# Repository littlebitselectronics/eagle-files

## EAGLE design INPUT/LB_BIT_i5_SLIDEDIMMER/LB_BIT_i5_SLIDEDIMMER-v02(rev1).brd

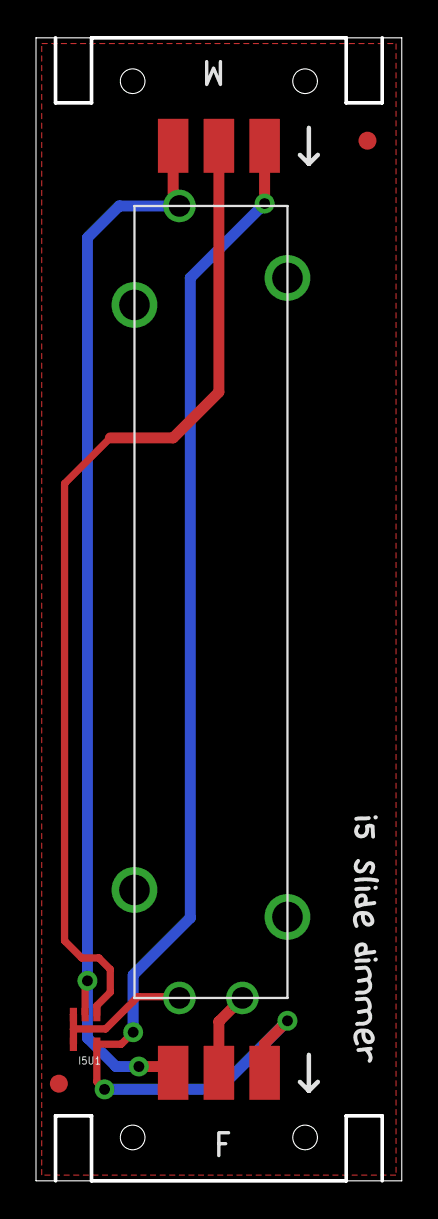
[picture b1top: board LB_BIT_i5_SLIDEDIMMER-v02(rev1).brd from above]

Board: 2 copper layers, 20.3 x 63.5 mm, 23 parts (0 on the bottom side), 5 nets.

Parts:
I5BSF: BITSNAP_FEMALE
I5BSM: BITSNAP_MALE
I5FD1, I5FD2: FIDUCIAL1X2; FIDUCIAL-1X2
I5R1: POT-SLIDE-30MM
I5U1: LV321; SC70
U$1, U$9, U$13: I
U$2: 5
U$3: S
U$4: L
U$5: OSHW-LOGOL; OSHW-LOGO-L
U$7: OSHW_FILLX150_NOTEXT
U$8: LB_V02
U$10, U$12: D
U$11, U$16: E
U$14, U$15: M
U$17: R
U$18: LB_CREDITS_V2

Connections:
GND: I5BSF.GND, I5BSM.GND, I5R1.3, I5U1.2
unnamed: I5R1.1, I5U1.3, I5U1.4
unnamed: I5BSM.SIG, I5U1.1
POT: I5BSF.SIG, I5R1.2
VCC: I5BSF.VCC, I5BSM.VCC, I5U1.5

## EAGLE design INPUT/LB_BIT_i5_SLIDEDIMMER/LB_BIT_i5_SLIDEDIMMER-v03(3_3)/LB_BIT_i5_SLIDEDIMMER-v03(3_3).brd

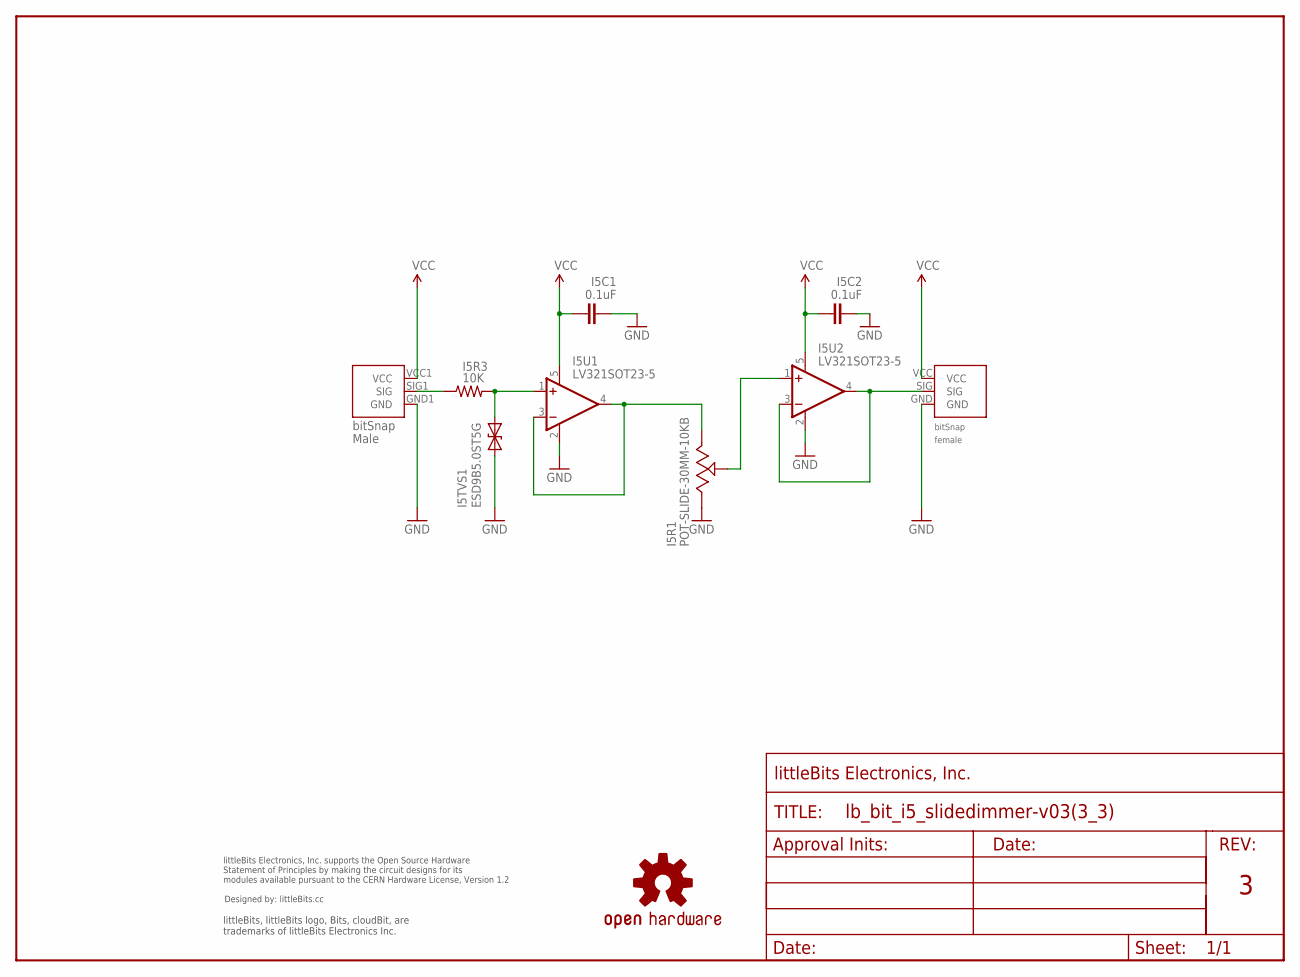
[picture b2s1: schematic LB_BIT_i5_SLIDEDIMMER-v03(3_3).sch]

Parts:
FRAME2: FRAME-LETTER-OHWOHW; FABDWG01-OHW
I5BSF1: BITSNAP_V03_FEMALE
I5BSM1: BITSNAP_V03_MALE
I5C1, I5C2: 0.1uF; CAP-0603
I5R1: POT-SLIDE-30MM-10KB; POT-SLIDE-30MM
I5R3: 10K; RES-0603
I5TVS1: ESD9B5.0ST5G; SOD-923
I5U1, I5U2: LV321SOT23-5; SOT23-5
U$1: OSHWCREDIT
U$5: OSHW-LOGOL; OSHW-LOGO-L

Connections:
GND: I5BSF1.GND, I5BSM1.GND1 (GND), I5C1.2, I5C2.2, I5R1.3, I5TVS1.1 (A), I5U1.2 (V-), I5U2.2 (V-)
unnamed: I5R1.1, I5U1.3 (-IN), I5U1.4 (OUT)
unnamed: I5BSM1.SIG1 (SIG), I5R3.1
unnamed: I5R3.2, I5TVS1.2 (C), I5U1.1 (+IN)
unnamed: I5R1.2, I5U2.1 (+IN)
unnamed: I5BSF1.SIG, I5U2.3 (-IN), I5U2.4 (OUT)
VCC: I5BSF1.VCC, I5BSM1.VCC1 (VCC), I5C1.1, I5C2.1, I5U1.5 (V+), I5U2.5 (V+)

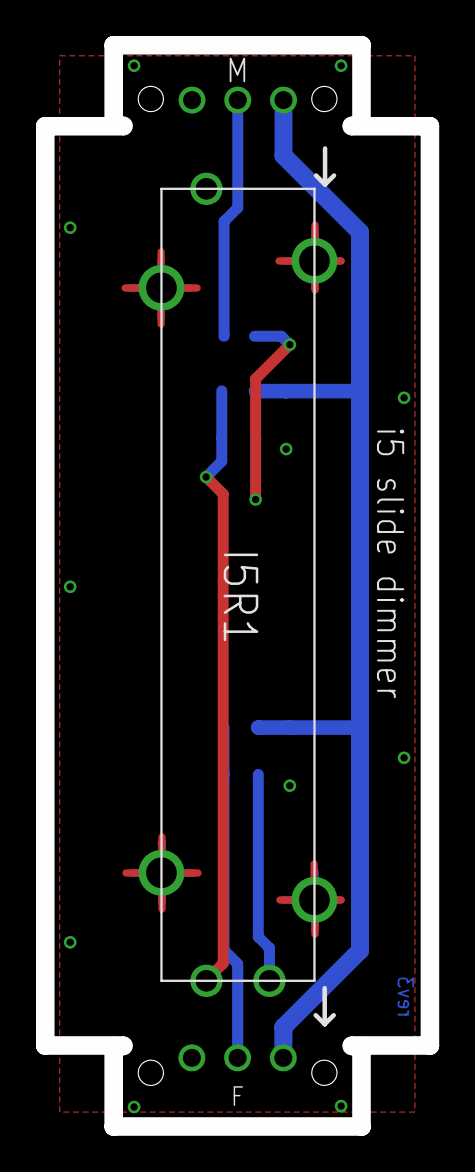
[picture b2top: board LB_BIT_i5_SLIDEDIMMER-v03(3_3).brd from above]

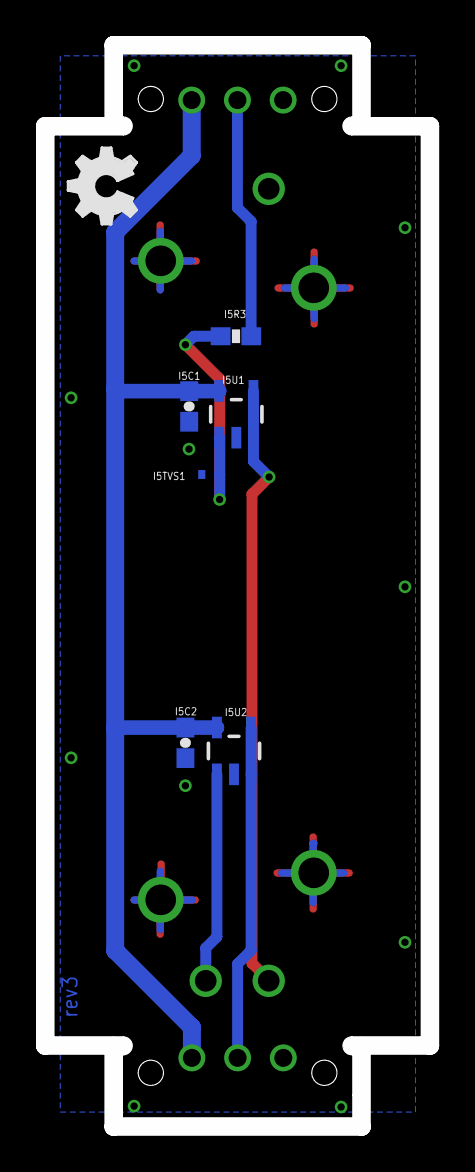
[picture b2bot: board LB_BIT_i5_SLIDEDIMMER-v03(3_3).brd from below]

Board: 2 copper layers, 21.4 x 60.1 mm, 13 parts (6 on the bottom side), 7 nets.

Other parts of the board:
U$7: OSHW_FILLX150_NOTEXT

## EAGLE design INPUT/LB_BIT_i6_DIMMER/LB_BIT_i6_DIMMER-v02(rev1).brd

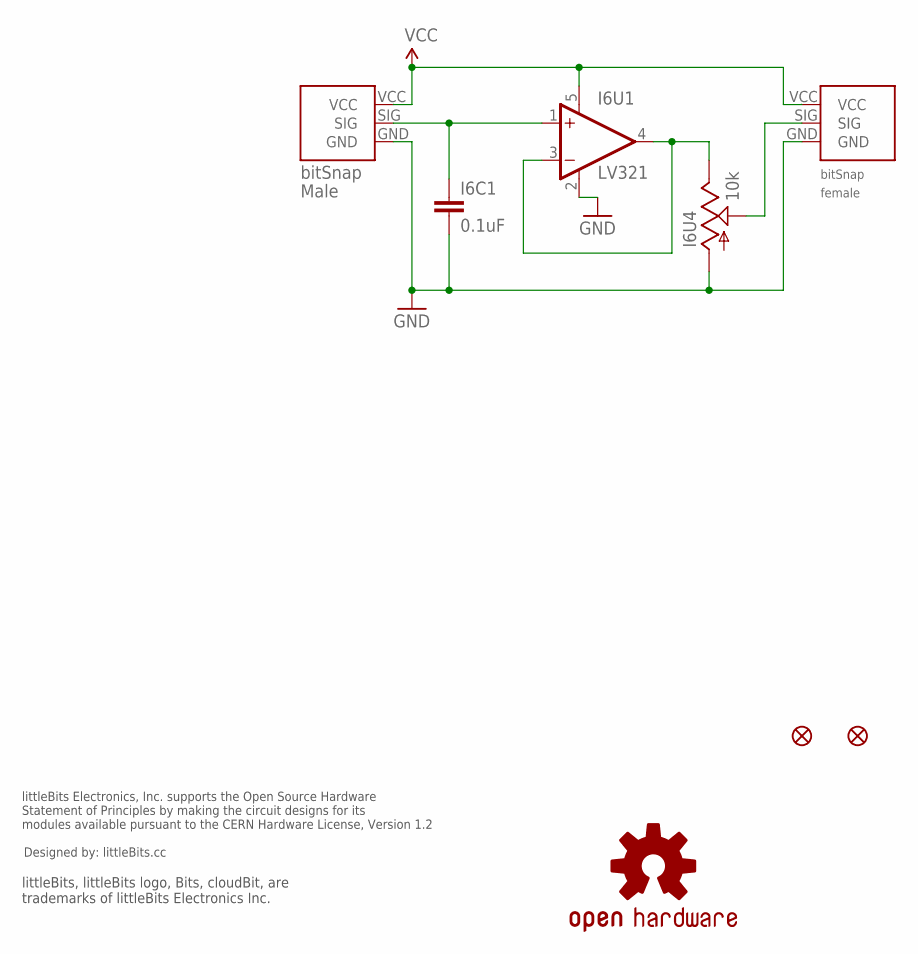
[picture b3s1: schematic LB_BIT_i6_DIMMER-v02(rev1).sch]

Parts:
I6BSF: BITSNAP_FEMALE
I6BSM: BITSNAP_MALE
I6C1: 0.1uF; 0603-CAP
I6U1: LV321; SC70-5
I6U4: 10k; ALPS_POT
JP1, JP2: FIDUCIAL1X2.5; FIDUCIAL-1X2.5
U$1: OSHWCREDIT
U$3: OSHW-LOGOL; OSHW-LOGO-L

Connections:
GND: I6BSF.GND, I6BSM.GND, I6C1.2, I6U1.2 (V-), I6U4.P$3 (A)
unnamed: I6U1.3 (-IN), I6U1.4 (OUT), I6U4.P$1 (E)
POT: I6BSF.SIG, I6U4.P$2 (S)
SIG: I6BSM.SIG, I6C1.1, I6U1.1 (+IN)
VCC: I6BSF.VCC, I6BSM.VCC, I6U1.5 (V+)

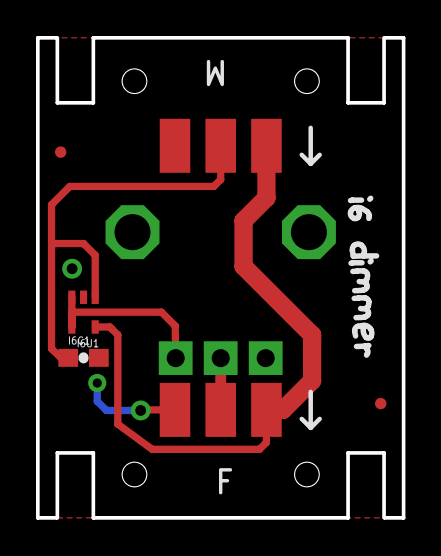
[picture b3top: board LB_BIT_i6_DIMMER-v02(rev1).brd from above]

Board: 2 copper layers, 20.3 x 26.7 mm, 9 parts (0 on the bottom side), 5 nets.

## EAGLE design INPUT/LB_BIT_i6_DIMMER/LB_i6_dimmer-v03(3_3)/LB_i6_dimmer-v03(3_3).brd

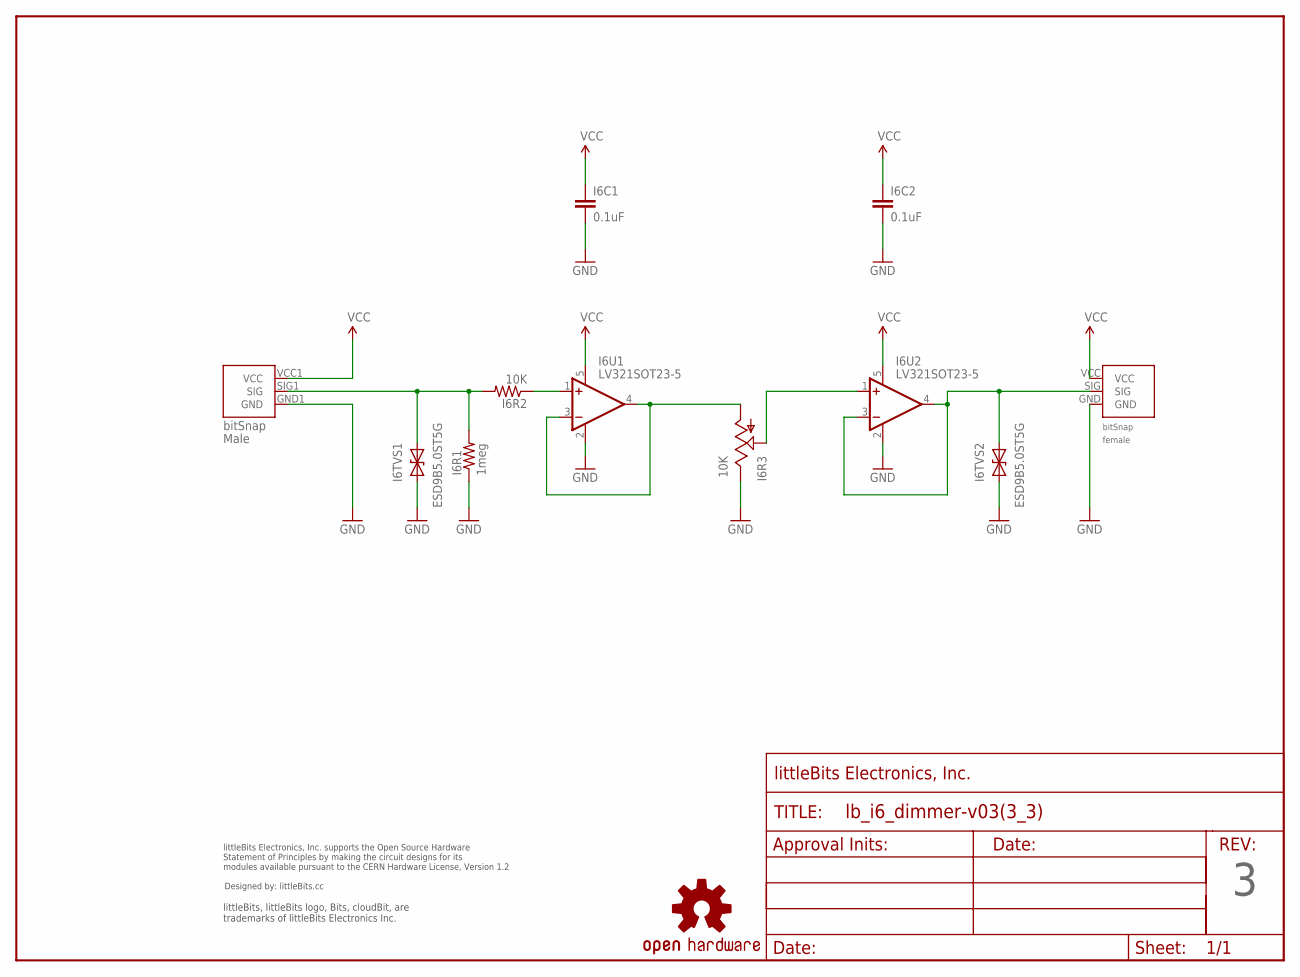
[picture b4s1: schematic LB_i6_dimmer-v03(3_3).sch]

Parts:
FRAME1: FRAME-LETTER-OHWOHW; FABDWG01-OHW
I6BSF1: BITSNAP_V03_FEMALE
I6BSM1: BITSNAP_V03_MALE
I6C1, I6C2: 0.1uF; CAP-0603
I6R1: 1meg; RES-0603
I6R2: 10K; RES-0603
I6R3: 10K; ALPS_POT
I6TVS1, I6TVS2: ESD9B5.0ST5G; SOD-923
I6U1, I6U2: LV321SOT23-5; SOT23-5
U$3: OSHW-LOGOL; OSHW-LOGO-L
U$4: LB_CREDITS; OSHWCREDIT

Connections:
GND: I6BSF1.GND, I6BSM1.GND1 (GND), I6C1.2, I6C2.2, I6R1.1, I6R3.P$1 (E), I6TVS1.1 (A), I6TVS2.1 (A), I6U1.2 (V-), I6U2.2 (V-)
unnamed: I6R3.P$3 (A), I6U1.3 (-IN), I6U1.4 (OUT)
unnamed: I6R2.1, I6U1.1 (+IN)
unnamed: I6BSF1.SIG, I6TVS2.2 (C), I6U2.3 (-IN), I6U2.4 (OUT)
unnamed: I6R3.P$2 (S), I6U2.1 (+IN)
SIG: I6BSM1.SIG1 (SIG), I6R1.2, I6R2.2, I6TVS1.2 (C)
VCC: I6BSF1.VCC, I6BSM1.VCC1 (VCC), I6C1.1, I6C2.1, I6U1.5 (V+), I6U2.5 (V+)

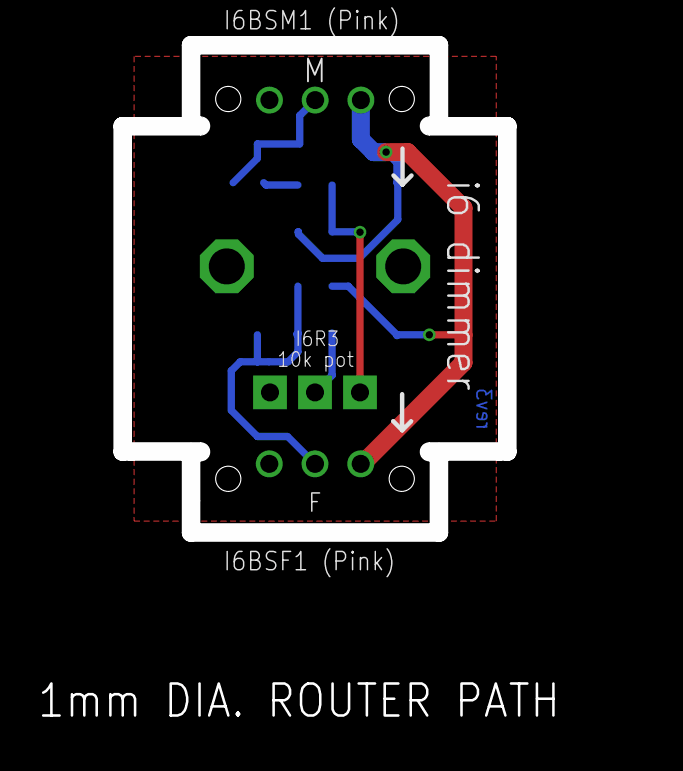
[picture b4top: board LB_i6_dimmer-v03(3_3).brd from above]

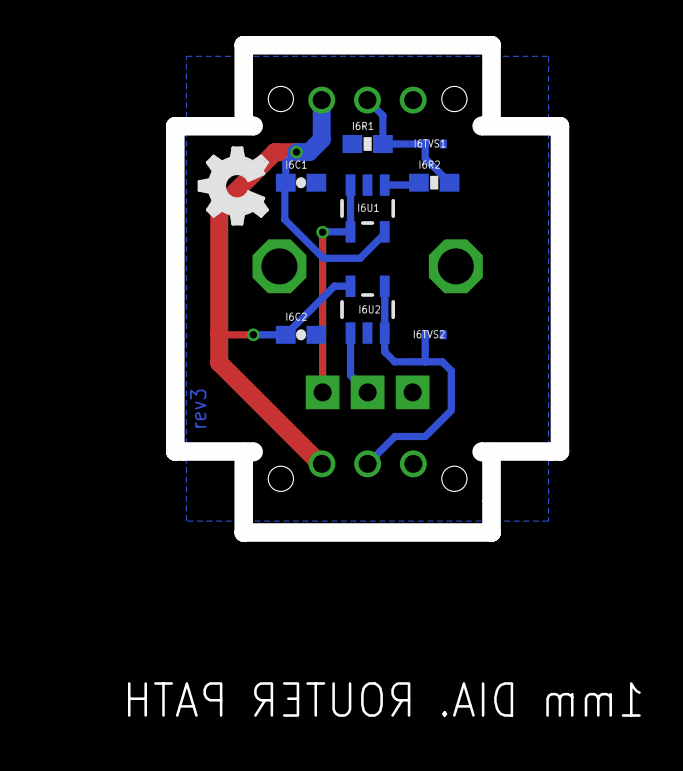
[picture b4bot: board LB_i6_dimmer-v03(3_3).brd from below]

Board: 2 copper layers, 21.4 x 27.1 mm, 15 parts (8 on the bottom side), 7 nets.

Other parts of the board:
U$1: OSHW_FILLX150_NOTEXT

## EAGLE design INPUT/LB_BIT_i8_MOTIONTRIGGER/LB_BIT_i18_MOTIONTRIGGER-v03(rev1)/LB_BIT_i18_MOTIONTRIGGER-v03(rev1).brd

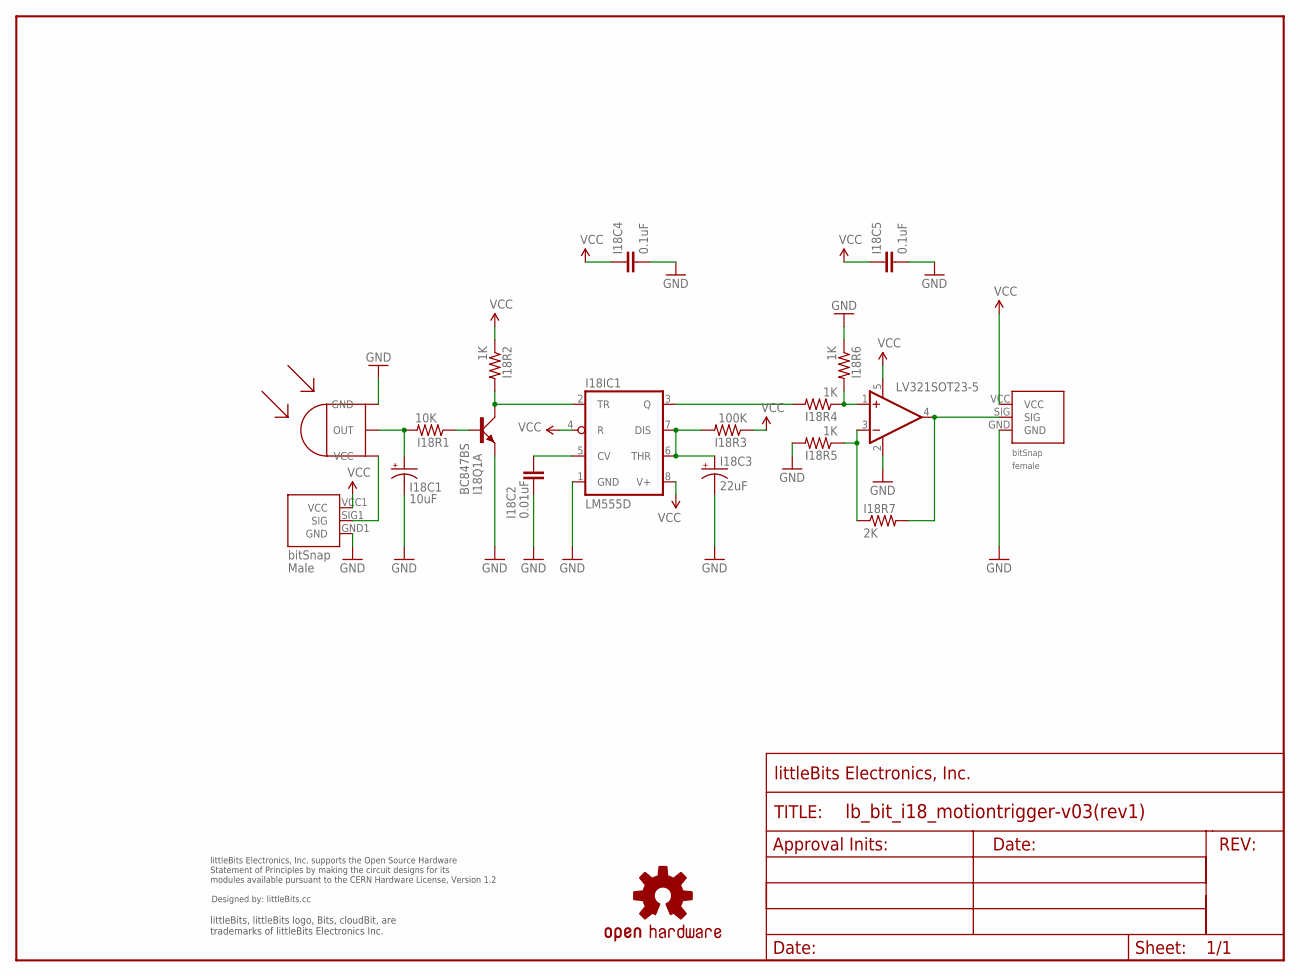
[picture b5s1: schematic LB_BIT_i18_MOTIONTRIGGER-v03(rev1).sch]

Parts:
I18BSF: BITSNAP_V03_FEMALE
I18BSM: BITSNAP_V03_MALE
I18C1: 10uF; EIA3216
I18C2: 0.01uF; 0603-CAP
I18C3: 22uF; EIA3216
I18C4, I18C5: 0.1uF; 0603-CAP
I18IC1: LM555D; SO08
I18Q1: BC847BS; SOT363_PHILIPS
I18R1: 10K; 0603-RES
I18R2, I18R4, I18R5, I18R6: 1K; 0603-RES
I18R3: 100K; 0603-RES
I18R7: 2K; 0603-RES
I18U1: PIR-EKMC1601112
I18U2: LV321SOT23-5; SOT23-5
U$1: OSHWCREDIT
U$2: FRAME-LETTER-OHWOHW; FABDWG01-OHW
U$8: OSHW-LOGOL; OSHW-LOGO-L

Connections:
GND: I18BSF.GND, I18BSM.GND1 (GND), I18C1.C (-), I18C2.2, I18C3.C (-), I18C4.2, I18C5.2, I18IC1.1 (GND), I18Q1.1 (E), I18R5.2, I18R6.1, I18U1.GND, I18U2.2 (V-)
unnamed: I18BSM.SIG1 (SIG), I18U1.VCC
unnamed: I18IC1.2 (TR), I18Q1.6 (C), I18R2.2
unnamed: I18C1.A (+), I18R1.2, I18U1.OUT
unnamed: I18Q1.2 (B), I18R1.1
unnamed: I18C2.1, I18IC1.5 (CV)
unnamed: I18C3.A (+), I18IC1.6 (THR), I18IC1.7 (DIS), I18R3.2
unnamed: I18IC1.3 (Q), I18R4.2
unnamed: I18R4.1, I18R6.2, I18U2.1 (+IN)
unnamed: I18R5.1, I18R7.1, I18U2.3 (-IN)
unnamed: I18BSF.SIG, I18R7.2, I18U2.4 (OUT)
VCC: I18BSF.VCC, I18BSM.VCC1 (VCC), I18C4.1, I18C5.1, I18IC1.4 (R), I18IC1.8 (V+), I18R2.1, I18R3.1, I18U2.5 (V+)

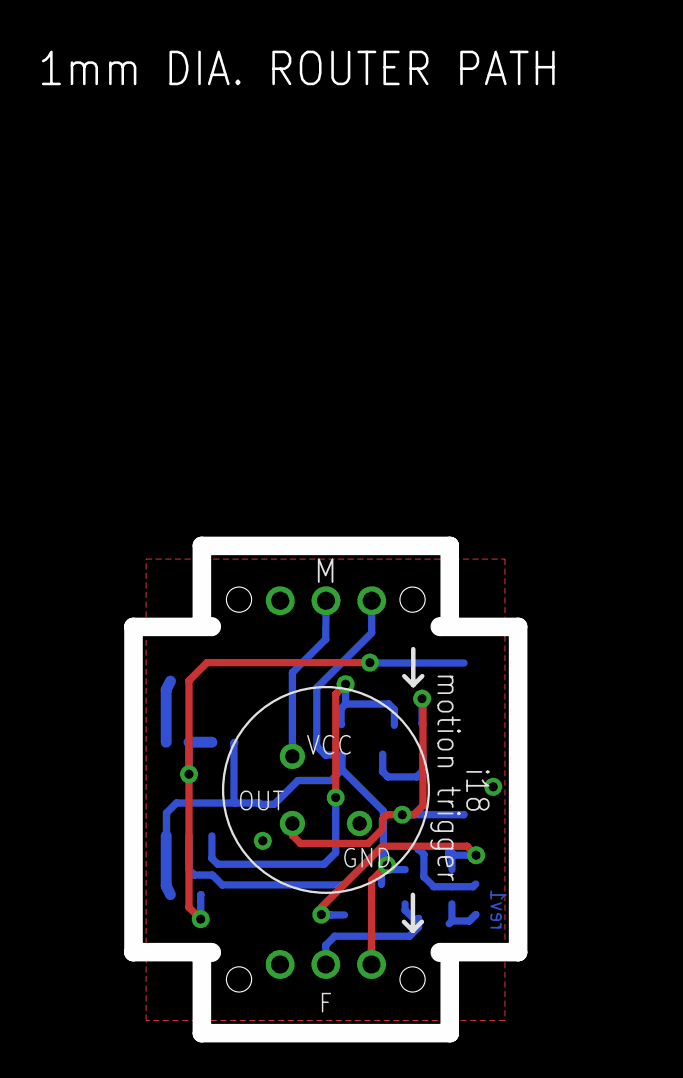
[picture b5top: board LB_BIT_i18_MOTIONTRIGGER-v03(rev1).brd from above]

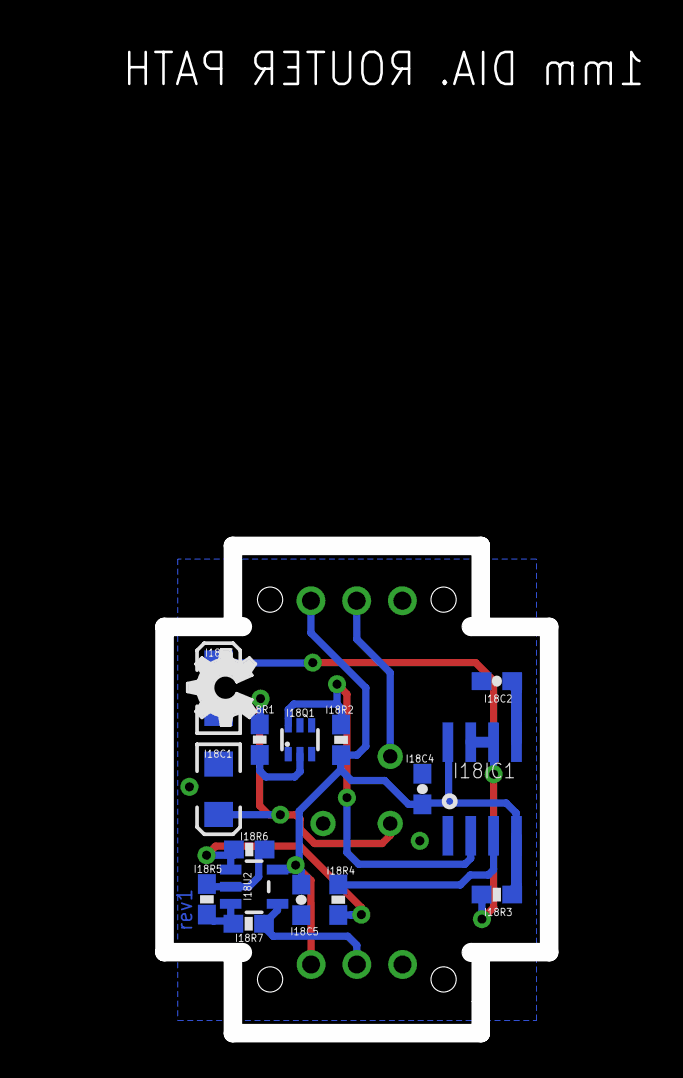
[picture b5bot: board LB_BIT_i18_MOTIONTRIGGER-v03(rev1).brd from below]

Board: 2 copper layers, 21.4 x 27.1 mm, 22 parts (15 on the bottom side), 12 nets.

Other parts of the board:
U$7: OSHW_FILLX150_NOTEXT

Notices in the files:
parts and their libraries:
LITTLEBITS: Released under the Creative Commons Attribution Share-Alike 3.0 License
LITTLEBITS: http://creativecommons.org/license/by-sa/3.0
SparkFun_NEW: Licensing: CC v3.0 Share-Alike You are welcome to use this library for commercial purposes.
